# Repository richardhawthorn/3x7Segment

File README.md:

### Features

- ESP8266 wifi processor
- 3 x 7 segment displays
- 3.3V operation
- Mini USB power connector
- FTDI chip and programming port

### License

This work is licensed under a Creative Commons Attribution-ShareAlike 4.0 International License.

<br />
Designed by <a xmlns:cc="http://creativecommons.org/ns#" href="http://www.richardhawthorn.com" property="cc:attributionName" rel="cc:attributionURL" target="_blank">Richard Hawthorn</a><br />
<a rel="license" href="http://creativecommons.org/licenses/by-sa/4.0/" target="_blank">View License</a>

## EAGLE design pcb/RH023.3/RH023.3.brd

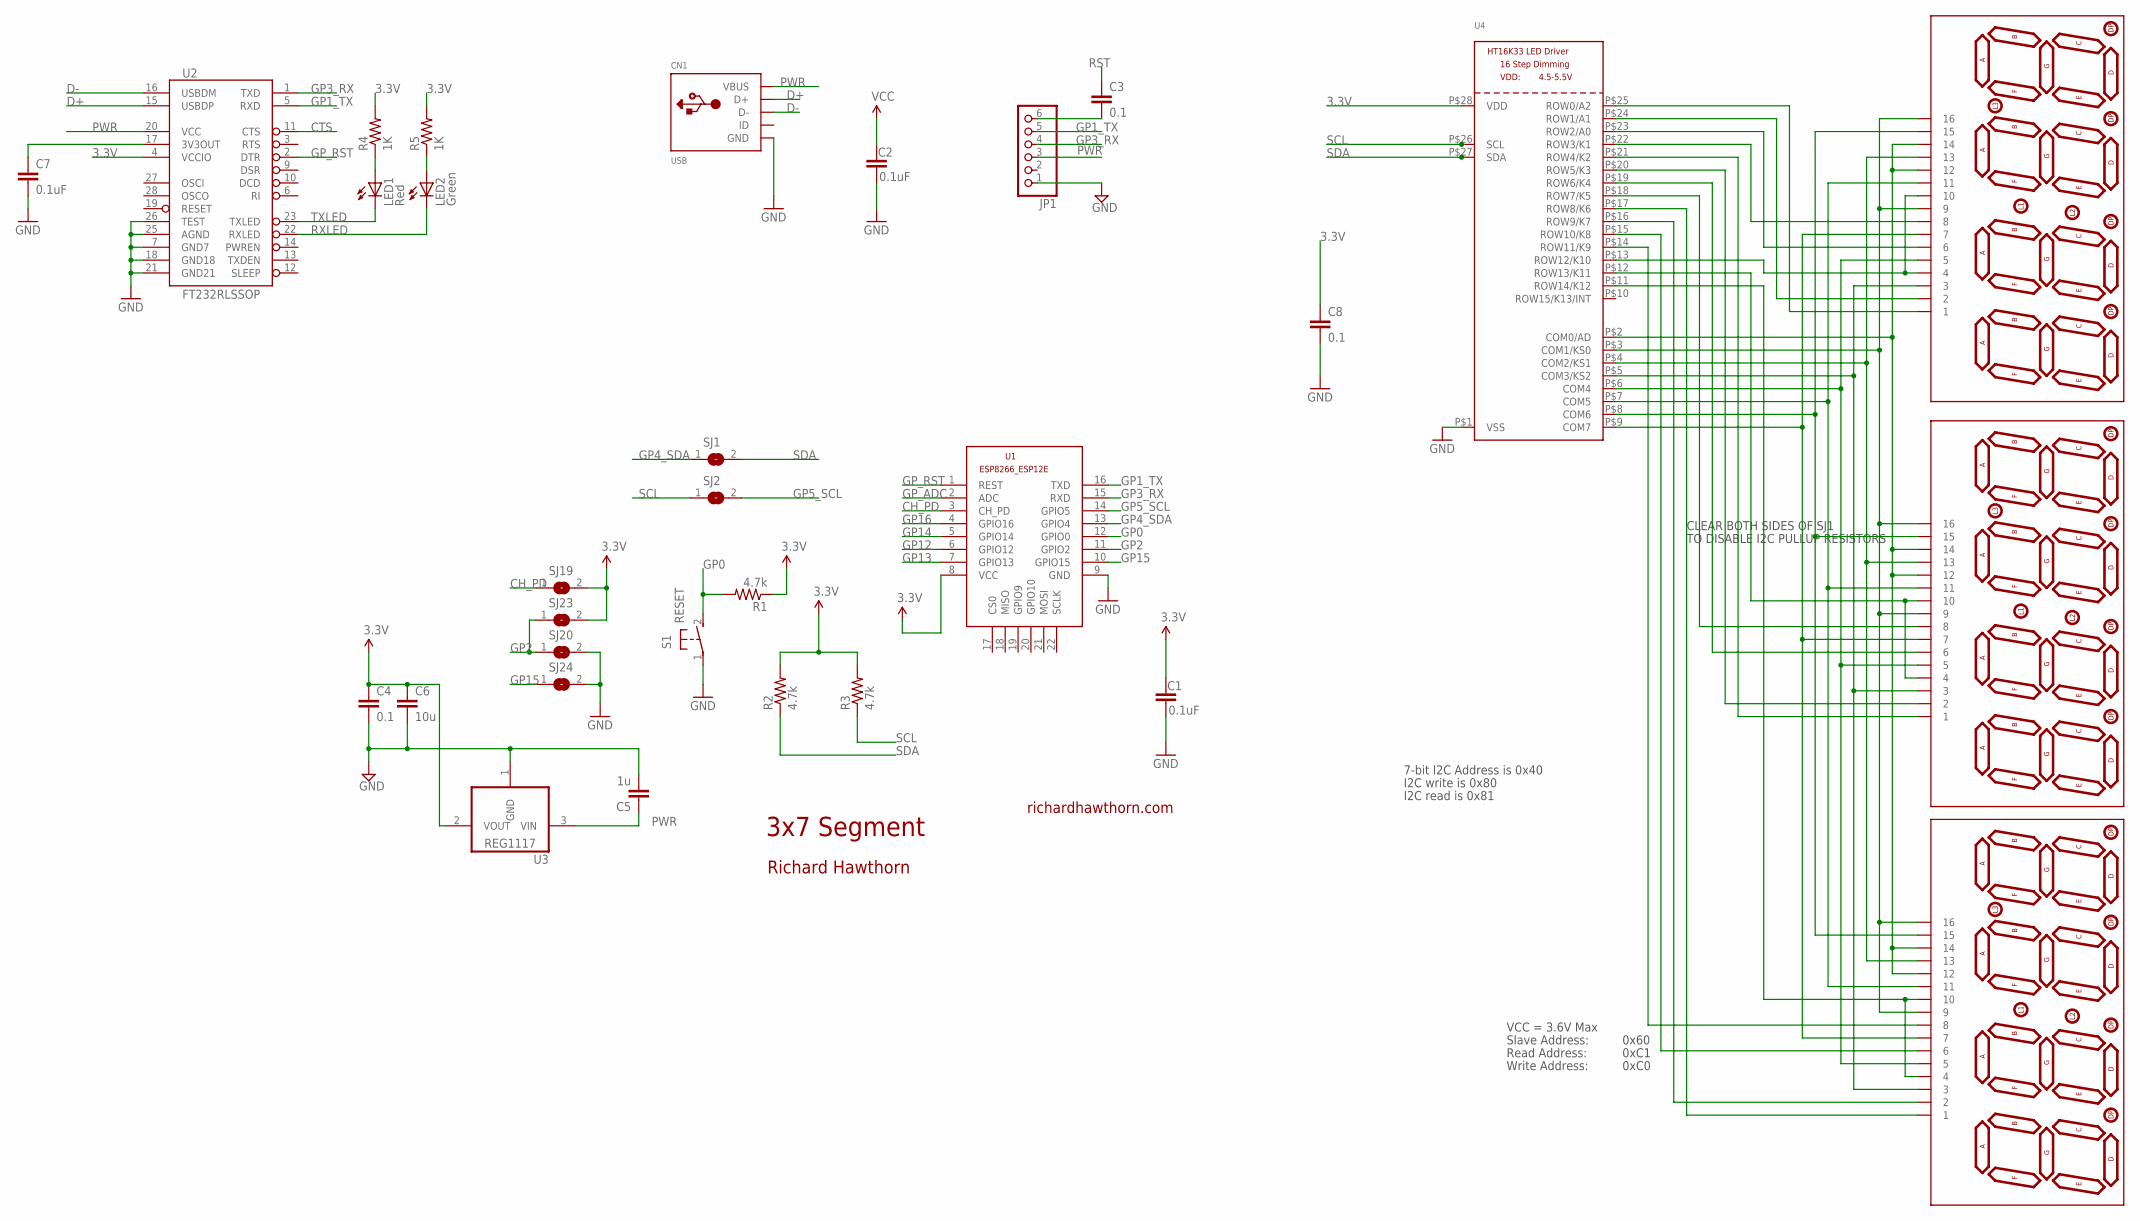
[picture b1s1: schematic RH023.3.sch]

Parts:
C1, C2: 0.1uF; 0603-CAP
C3, C4, C8: 0.1; 0603-CAP
C5: 1u; 0603-CAP
C6: 10u; 0805-CAP
C7: 0.1uF; 0402-CAP
CN1: USB; USB-MINIB
JP1: PINHD-1X6; 1X06
LED1: Red; LED-0603
LED2: Green; LED-0603
LED3, LED4, LED5: 7SEG-4DIGIT; SPARKFUN_7-SEGMENT-4DIGIT
R1, R2, R3: 4.7k; 0805
R4, R5: 1K; 0402-RES
S1: RESET; DTSM-3
SJ1, SJ2, SJ19, SJ20, SJ23, SJ24: SJ
U1: ESP8266-12EESP8266-ESP12E; ESP8266-ESP12E
U2: FT232RLSSOP; SSOP28DB
U3: REG1117; SOT223
U4: HT16K33_SOP28; SOP28_300MIL

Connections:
3.3V: C1.1, C2.1, C4.1, C6.1, C8.1, R1.1, R2.2, R3.2, R4.2, R5.2, SJ19.2, SJ23.2, U1.8 (VCC), U2.4 (VCCIO), U3.2 (VOUT), U4.P$28 (VDD)
3.3VOUT: C7.1, U2.17 (3V3OUT)
CH_PD: SJ19.1, U1.3 (CH_PD)
CTS: U2.11 (CTS)
D+: CN1.D+, U2.15 (USBDP)
D-: CN1.D-, U2.16 (USBDM)
GND: C1.2, C2.2, C4.2, C5.2, C6.2, C7.2, C8.2, CN1.GND, JP1.1, S1.1, SJ20.2, SJ24.2, U1.9 (GND), U2.7 (GND7), U2.18 (GND18), U2.21 (GND21), U2.25 (AGND), U2.26 (TEST), U3.1 (GND), U4.P$1 (VSS)
GP0: R1.2, S1.2, U1.12 (GPIO0)
GP1_TX: JP1.5, U1.16 (TXD), U2.5 (RXD)
GP2: SJ20.1, SJ23.1, U1.11 (GPIO2)
GP3_RX: JP1.4, U1.15 (RXD), U2.1 (TXD)
GP4_SDA: SJ1.1, U1.13 (GPIO4)
GP5_SCL: SJ2.2, U1.14 (GPIO5)
GP12: U1.6 (GPIO12)
GP13: U1.7 (GPIO13)
GP14: U1.5 (GPIO14)
GP15: SJ24.1, U1.10 (GPIO15)
GP16: U1.4 (GPIO16)
GP_ADC: U1.2 (ADC)
GP_RST: U1.1 (REST), U2.2 (DTR)
unnamed: LED3.12, LED3.14, LED4.12, LED4.14, LED5.12, LED5.14, U4.P$2 (COM0/AD)
unnamed: LED1.A, R4.1
unnamed: LED2.A, R5.1
unnamed: LED3.9, LED3.16, LED4.9, LED4.16, LED5.9, LED5.16, U4.P$3 (COM1/KS0)
unnamed: LED3.13, LED4.13, LED5.13, U4.P$4 (COM2/KS1)
unnamed: LED3.3, LED4.3, LED5.3, U4.P$5 (COM3/KS2)
unnamed: LED3.5, LED4.5, LED5.5, U4.P$6 (COM4)
unnamed: LED3.11, LED4.11, LED5.11, U4.P$7 (COM5)
unnamed: LED3.15, LED4.15, LED5.15, U4.P$8 (COM6)
unnamed: LED3.7, LED4.7, LED5.7, U4.P$9 (COM7)
unnamed: LED3.1, U4.P$25 (ROW0/A2)
unnamed: LED3.2, U4.P$24 (ROW1/A1)
unnamed: LED3.6, U4.P$23 (ROW2/A0)
unnamed: LED3.8, U4.P$22 (ROW3/K1)
unnamed: LED4.1, U4.P$21 (ROW4/K2)
unnamed: LED4.2, U4.P$20 (ROW5/K3)
unnamed: LED4.6, U4.P$19 (ROW6/K4)
unnamed: LED4.8, U4.P$18 (ROW7/K5)
unnamed: LED5.1, U4.P$17 (ROW8/K6)
unnamed: C3.2, JP1.6
unnamed: LED5.2, U4.P$16 (ROW9/K7)
unnamed: LED5.6, U4.P$15 (ROW10/K8)
unnamed: LED5.8, U4.P$14 (ROW11/K9)
unnamed: LED3.4, LED3.10, U4.P$13 (ROW12/K10)
unnamed: LED4.4, LED4.10, U4.P$12 (ROW13/K11)
unnamed: LED5.4, LED5.10, U4.P$11 (ROW14/K12)
PWR: C5.1, CN1.VBUS, JP1.3, U2.20 (VCC), U3.3 (VIN)
RST: C3.1
RXLED: LED2.C, U2.22 (RXLED)
SCL: R3.1, SJ2.1, U4.P$26 (SCL)
SDA: R2.1, SJ1.2, U4.P$27 (SDA)
TXLED: LED1.C, U2.23 (TXLED)

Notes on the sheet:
3x7 Segment
richardhawthorn.com
Richard Hawthorn
CLEAR BOTH SIDES OF SJ1
TO DISABLE I2C PULLUP RESISTORS
7-bit I2C Address is 0x40
I2C write is 0x80
I2C read is 0x81
VCC = 3.6V Max
Read Address:
Write Address:
Slave Address:
0x60
0xC1
0xC0

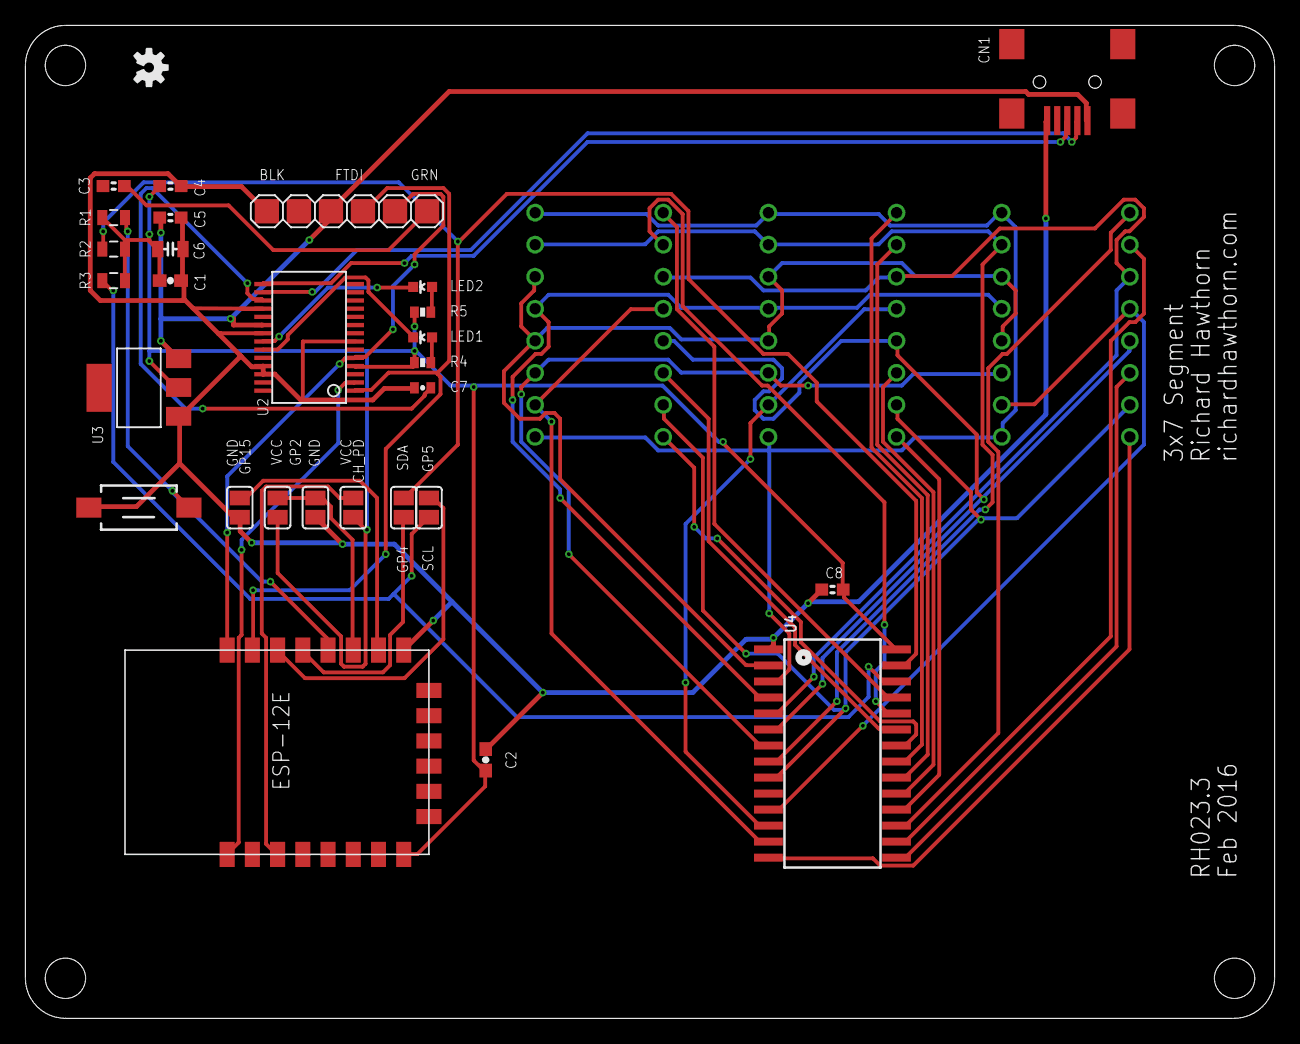
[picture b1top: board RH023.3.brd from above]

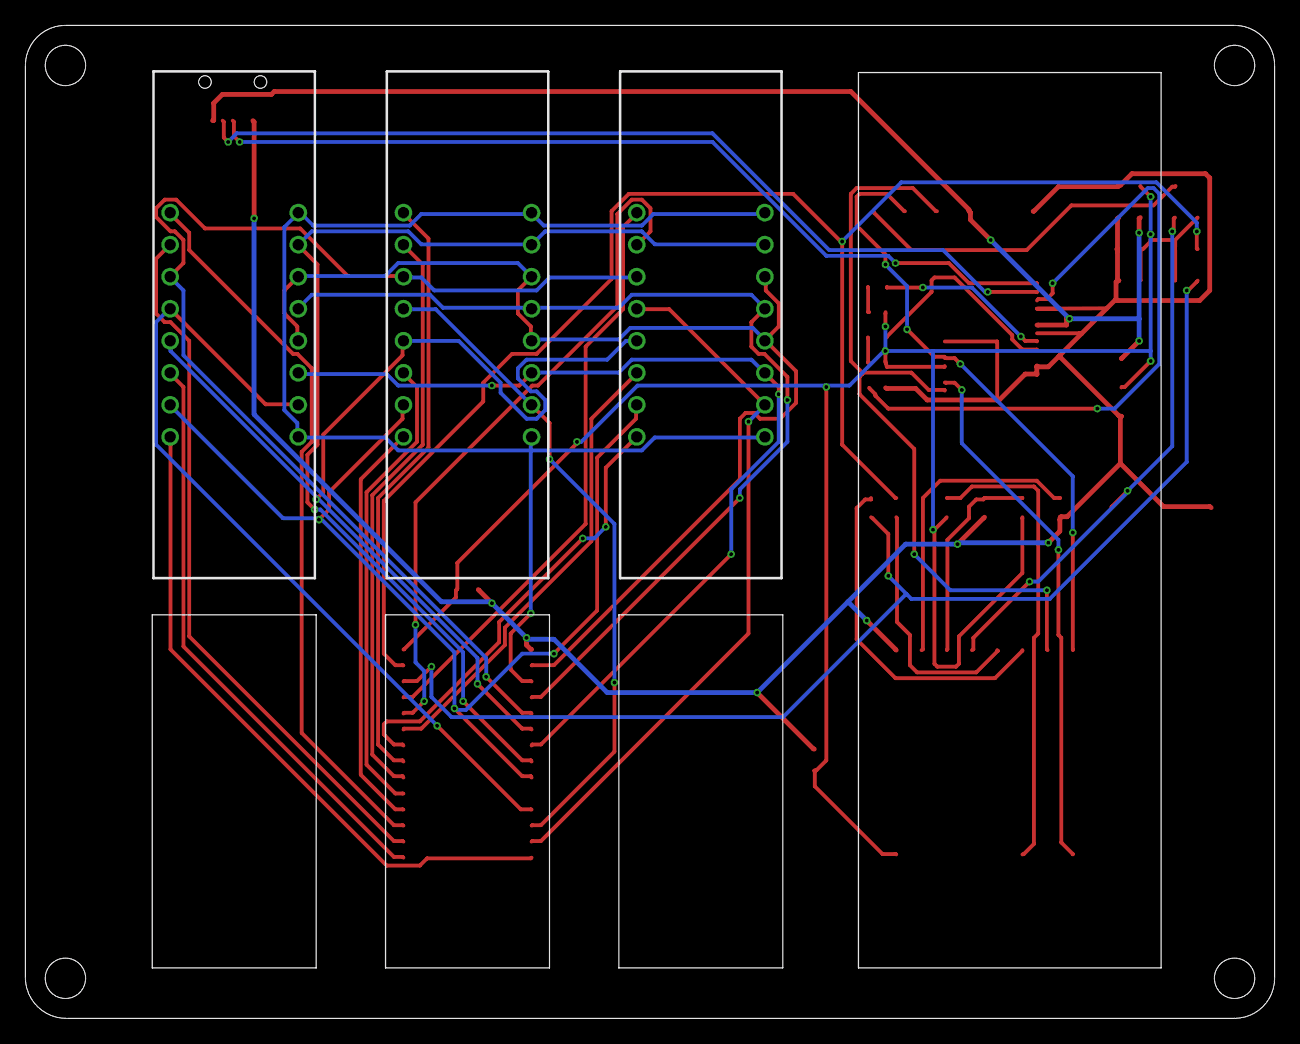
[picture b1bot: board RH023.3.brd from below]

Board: 2 copper layers, 99.1 x 78.7 mm, 32 parts (3 on the bottom side), 45 nets.

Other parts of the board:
U$3: OSHW-LOGO-S

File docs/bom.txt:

Part     Value          Device 

C1       0.1uF          CAP0805-CAP 
C2       0.1uF          CAP0805-CAP 
C3       0.1uF          CAP0805-CAP 
C4       0.1uF          CAP0805-CAP 
C5       1uF            CAP0805-CAP 
C6       10uF           CAP0805-CAP 
C8       0.1uF          CAP0805-CAP 
CN1      USB            USB-MINI-B 
JP1      FTDI           PINHD-1X6 
LED3     7SEG-4DIGIT    7SEG-4DIGIT  
LED4     7SEG-4DIGIT    7SEG-4DIGIT 
LED5     7SEG-4DIGIT    7SEG-4DIGIT 
R1       4.7k           RESISTOR0805-RES 
R2       4.7k           RESISTOR0805-RES 
R3       4.7k           RESISTOR0805-RES 
S1       RESET          DTSM-3  
U1       ESP8266        ESP8266-ESP12E 
U3       REG1117        REG1117 
U4       HT16K33        HT16K33_SOP28

Future Upgrade

U2       FT232RLSSOP    FT232RLSSOP 
C7       0.1uF          CAP0805-CAP 
R4       1K             RESISTOR0402-RES 
R5       1K             RESISTOR0402-RES 
LED1     Red            LED0603 
LED2     Green          LED0603

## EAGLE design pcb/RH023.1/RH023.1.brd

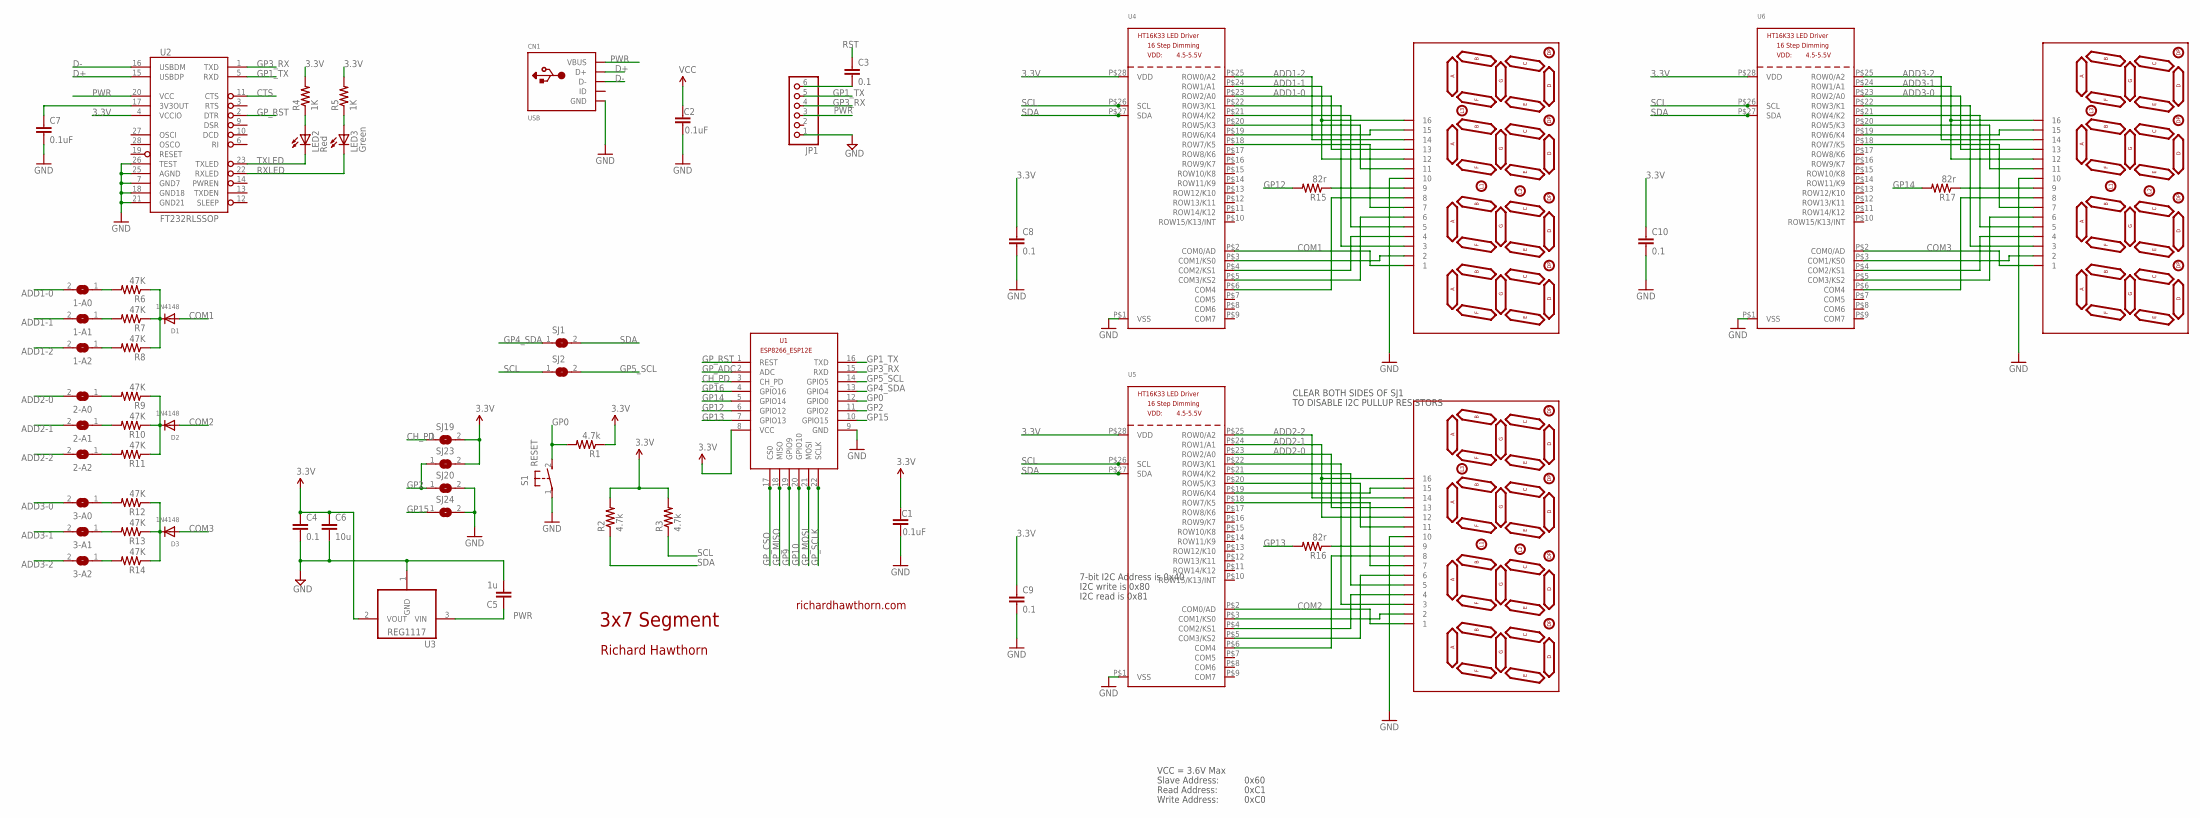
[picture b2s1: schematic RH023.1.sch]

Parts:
1-A0, 1-A1, 1-A2, 2-A0, 2-A1, 2-A2, 3-A0, 3-A1, 3-A2: SOLDERJUMPERREFLOW_NOPASTE; SOLDERJUMPER_REFLOW_NOPASTE
C1, C2: 0.1uF; 0603-CAP
C3, C4, C8, C9, C10: 0.1; 0603-CAP
C5: 1u; 0603-CAP
C6: 10u; 0805-CAP
C7: 0.1uF; 0402-CAP
CN1: USB; USB-MINIB
D1, D2, D3: 1N4148; SOD-323F
JP1: PINHD-1X6; 1X06
LED1, LED4, LED5: 7SEG-4DIGIT; SPARKFUN_7-SEGMENT-4DIGIT
LED2: Red; LED-0603
LED3: Green; LED-0603
R1, R2, R3: 4.7k; 0805
R4, R5: 1K; 0402-RES
R6, R7, R8, R9, R10, R11, R12, R13, R14: 47K; R0805
R15, R16, R17: 82r; 0805
S1: RESET; DTSM-3
SJ1, SJ2, SJ19, SJ20, SJ23, SJ24: SJ
U1: ESP8266-12EESP8266-ESP12E; ESP8266-ESP12E
U2: FT232RLSSOP; SSOP28DB
U3: REG1117; SOT223
U4, U5, U6: HT16K33_SOP28; SOP28_300MIL

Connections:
3.3V: C1.1, C2.1, C4.1, C6.1, C8.1, C9.1, C10.1, R1.1, R2.2, R3.2, R4.2, R5.2, SJ19.2, SJ23.2, U1.8 (VCC), U2.4 (VCCIO), U3.2 (VOUT), U4.P$28 (VDD), U5.P$28 (VDD), U6.P$28 (VDD)
3.3VOUT: C7.1, U2.17 (3V3OUT)
ADD1-0: 1-A0.2, LED1.13, U4.P$23 (ROW2/A0)
ADD1-1: 1-A1.2, LED1.12, LED1.16, U4.P$24 (ROW1/A1)
ADD1-2: 1-A2.2, LED1.14, U4.P$25 (ROW0/A2)
ADD2-0: 2-A0.2, LED4.13, U5.P$23 (ROW2/A0)
ADD2-1: 2-A1.2, LED4.12, LED4.16, U5.P$24 (ROW1/A1)
ADD2-2: 2-A2.2, LED4.14, U5.P$25 (ROW0/A2)
ADD3-0: 3-A0.2, LED5.13, U6.P$23 (ROW2/A0)
ADD3-1: 3-A1.2, LED5.12, LED5.16, U6.P$24 (ROW1/A1)
ADD3-2: 3-A2.2, LED5.14, U6.P$25 (ROW0/A2)
CH_PD: SJ19.1, U1.3 (CH_PD)
COM1: D1.A, LED1.1, U4.P$2 (COM0/AD)
COM2: D2.A, LED4.1, U5.P$2 (COM0/AD)
COM3: D3.A, LED5.1, U6.P$2 (COM0/AD)
CTS: U2.11 (CTS)
D+: CN1.D+, U2.15 (USBDP)
D-: CN1.D-, U2.16 (USBDM)
GND: C1.2, C2.2, C4.2, C5.2, C6.2, C7.2, C8.2, C9.2, C10.2, CN1.GND, JP1.1, LED1.10, LED4.10, LED5.10, S1.1, SJ20.2, SJ24.2, U1.9 (GND), U2.7 (GND7), U2.18 (GND18), U2.21 (GND21), U2.25 (AGND), U2.26 (TEST), U3.1 (GND), U4.P$1 (VSS), U5.P$1 (VSS), U6.P$1 (VSS)
GP0: R1.2, S1.2, U1.12 (GPIO0)
GP1_TX: JP1.5, U1.16 (TXD), U2.5 (RXD)
GP2: SJ20.1, SJ23.1, U1.11 (GPIO2)
GP3_RX: JP1.4, U1.15 (RXD), U2.1 (TXD)
GP4_SDA: SJ1.1, U1.13 (GPIO4)
GP5_SCL: SJ2.2, U1.14 (GPIO5)
GP9: U1.19 (GPIO9)
GP10: U1.20 (GPIO10)
GP12: R15.2, U1.6 (GPIO12)
GP13: R16.2, U1.7 (GPIO13)
GP14: R17.2, U1.5 (GPIO14)
GP15: SJ24.1, U1.10 (GPIO15)
GP16: U1.4 (GPIO16)
GP_ADC: U1.2 (ADC)
GP_CSO: U1.17 (CS0)
GP_MISO: U1.18 (MISO)
GP_MOSI: U1.21 (MOSI)
GP_RST: U1.1 (REST), U2.2 (DTR)
GP_SCLK: U1.22 (SCLK)
unnamed: LED1.9, R15.1
unnamed: LED2.A, R4.1
unnamed: LED3.A, R5.1
unnamed: 2-A1.1, R10.2
unnamed: 1-A0.1, R6.2
unnamed: LED1.11, U4.P$20 (ROW5/K3)
unnamed: LED1.2, U4.P$3 (COM1/KS0)
unnamed: LED1.4, U4.P$4 (COM2/KS1)
unnamed: LED1.6, U4.P$5 (COM3/KS2)
unnamed: LED1.8, U4.P$6 (COM4)
unnamed: LED1.3, U4.P$22 (ROW3/K1)
unnamed: LED1.5, U4.P$21 (ROW4/K2)
unnamed: 2-A0.1, R9.2
unnamed: LED1.7, U4.P$18 (ROW7/K5)
unnamed: LED1.15, U4.P$19 (ROW6/K4)
unnamed: D2.C, R9.1, R10.1, R11.1
unnamed: D1.C, R6.1, R7.1, R8.1
unnamed: 1-A2.1, R8.2
unnamed: 1-A1.1, R7.2
unnamed: C3.2, JP1.6
unnamed: 2-A2.1, R11.2
unnamed: 3-A1.1, R13.2
unnamed: 3-A0.1, R12.2
unnamed: D3.C, R12.1, R13.1, R14.1
unnamed: 3-A2.1, R14.2
unnamed: LED4.2, U5.P$3 (COM1/KS0)
unnamed: LED4.4, U5.P$4 (COM2/KS1)
unnamed: LED4.6, U5.P$5 (COM3/KS2)
unnamed: LED4.8, U5.P$6 (COM4)
unnamed: LED4.3, U5.P$22 (ROW3/K1)
unnamed: LED4.5, U5.P$21 (ROW4/K2)
unnamed: LED4.15, U5.P$19 (ROW6/K4)
unnamed: LED4.11, U5.P$20 (ROW5/K3)
unnamed: LED4.7, U5.P$18 (ROW7/K5)
unnamed: LED4.9, R16.1
unnamed: LED5.2, U6.P$3 (COM1/KS0)
unnamed: LED5.4, U6.P$4 (COM2/KS1)
unnamed: LED5.6, U6.P$5 (COM3/KS2)
unnamed: LED5.8, U6.P$6 (COM4)
unnamed: LED5.3, U6.P$22 (ROW3/K1)
unnamed: LED5.5, U6.P$21 (ROW4/K2)
unnamed: LED5.15, U6.P$19 (ROW6/K4)
unnamed: LED5.11, U6.P$20 (ROW5/K3)
unnamed: LED5.7, U6.P$18 (ROW7/K5)
unnamed: LED5.9, R17.1
PWR: C5.1, CN1.VBUS, JP1.3, U2.20 (VCC), U3.3 (VIN)
RST: C3.1
RXLED: LED3.C, U2.22 (RXLED)
SCL: R3.1, SJ2.1, U4.P$26 (SCL), U5.P$26 (SCL), U6.P$26 (SCL)
SDA: R2.1, SJ1.2, U4.P$27 (SDA), U5.P$27 (SDA), U6.P$27 (SDA)
TXLED: LED2.C, U2.23 (TXLED)

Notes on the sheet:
3x7 Segment
richardhawthorn.com
Richard Hawthorn
CLEAR BOTH SIDES OF SJ1
TO DISABLE I2C PULLUP RESISTORS
7-bit I2C Address is 0x40
I2C write is 0x80
I2C read is 0x81
VCC = 3.6V Max
Read Address:
Write Address:
Slave Address:
0x60
0xC1
0xC0

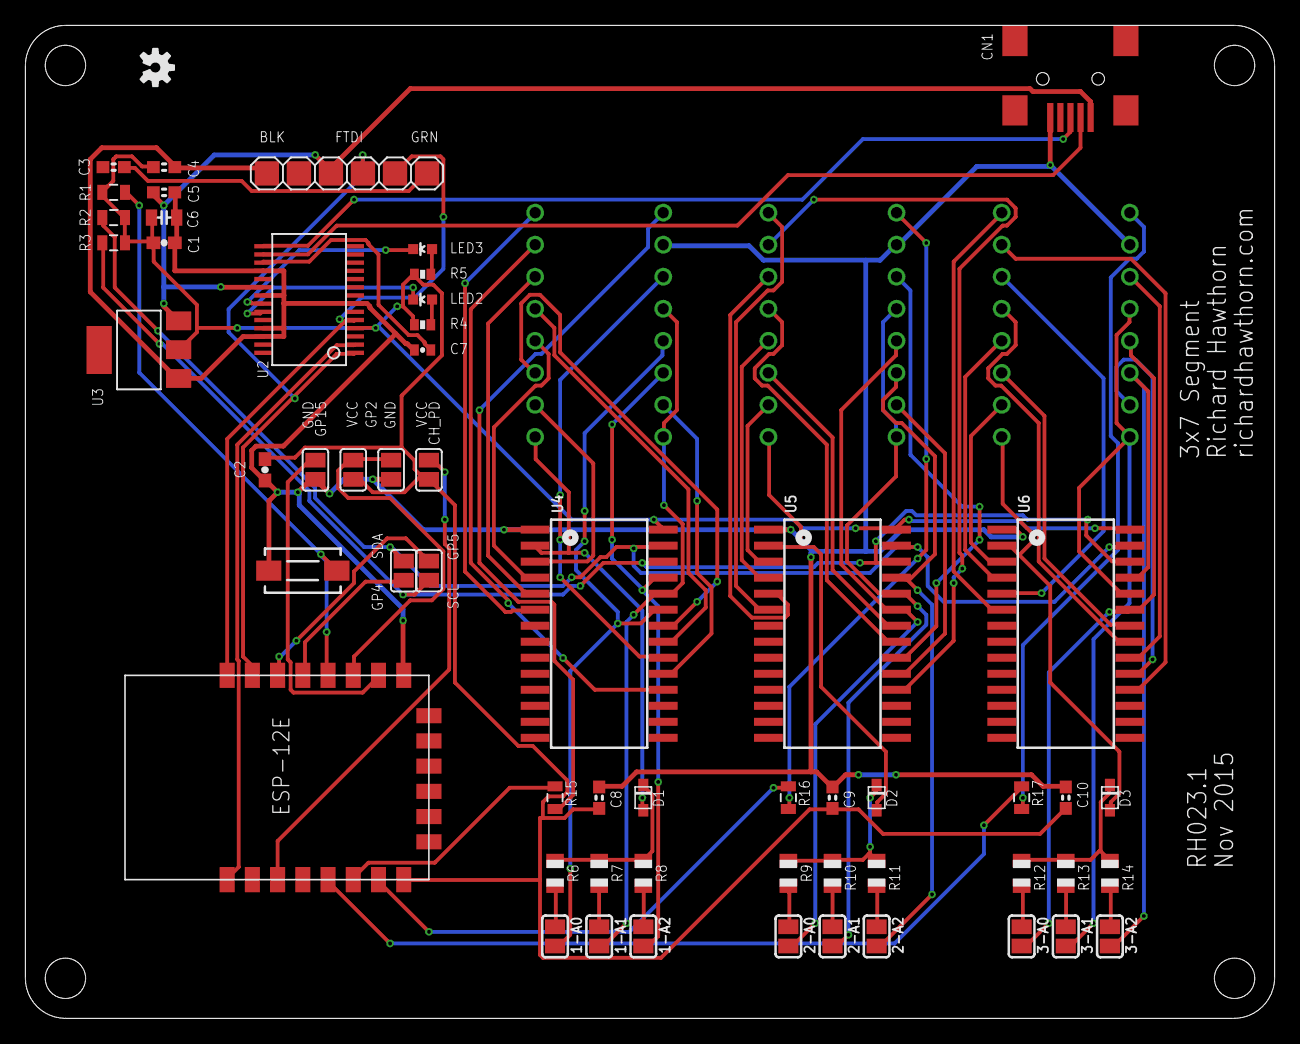
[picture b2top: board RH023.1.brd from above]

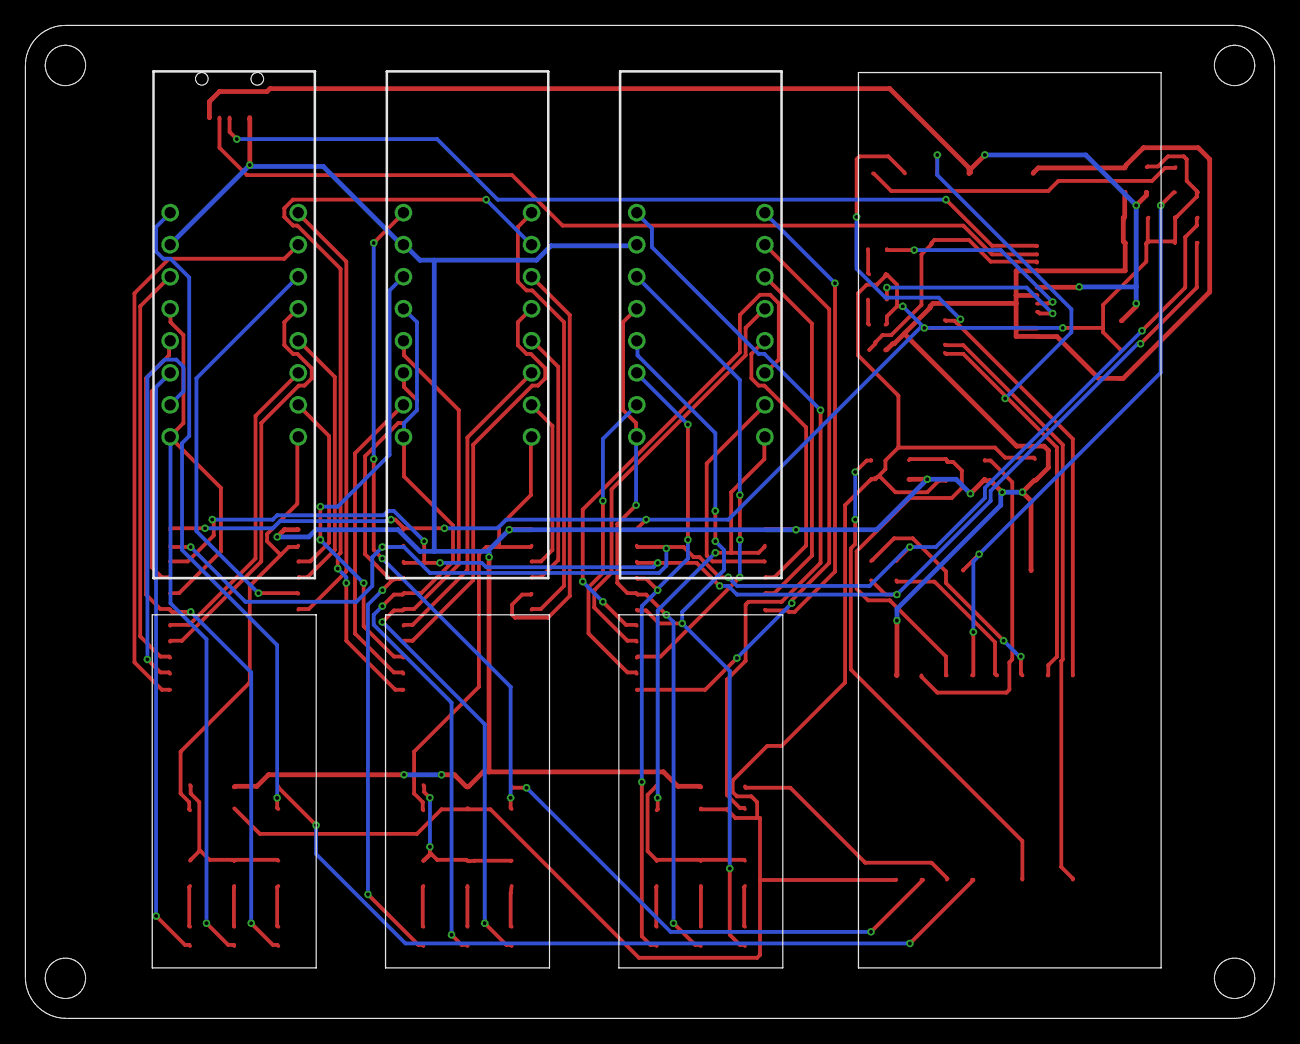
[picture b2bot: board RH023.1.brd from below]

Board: 2 copper layers, 99.1 x 78.7 mm, 60 parts (3 on the bottom side), 79 nets.

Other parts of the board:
U$3: OSHW-LOGO-S

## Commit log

2015-12-01 first version of the pcb
2015-12-01 second version, gerbers and images
2015-12-01 fixed unattached nets
2015-12-22 added a BOM
2016-11-08 add v3 of the pcb
2016-11-08 Arduino code for v2 of the board
2016-11-10 add readme
2017-01-24 adding images

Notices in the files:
parts and their libraries:
SparkFun-Aesthetics: Licensing: CC v3.0 Share-Alike You are welcome to use this library for commercial purposes.
